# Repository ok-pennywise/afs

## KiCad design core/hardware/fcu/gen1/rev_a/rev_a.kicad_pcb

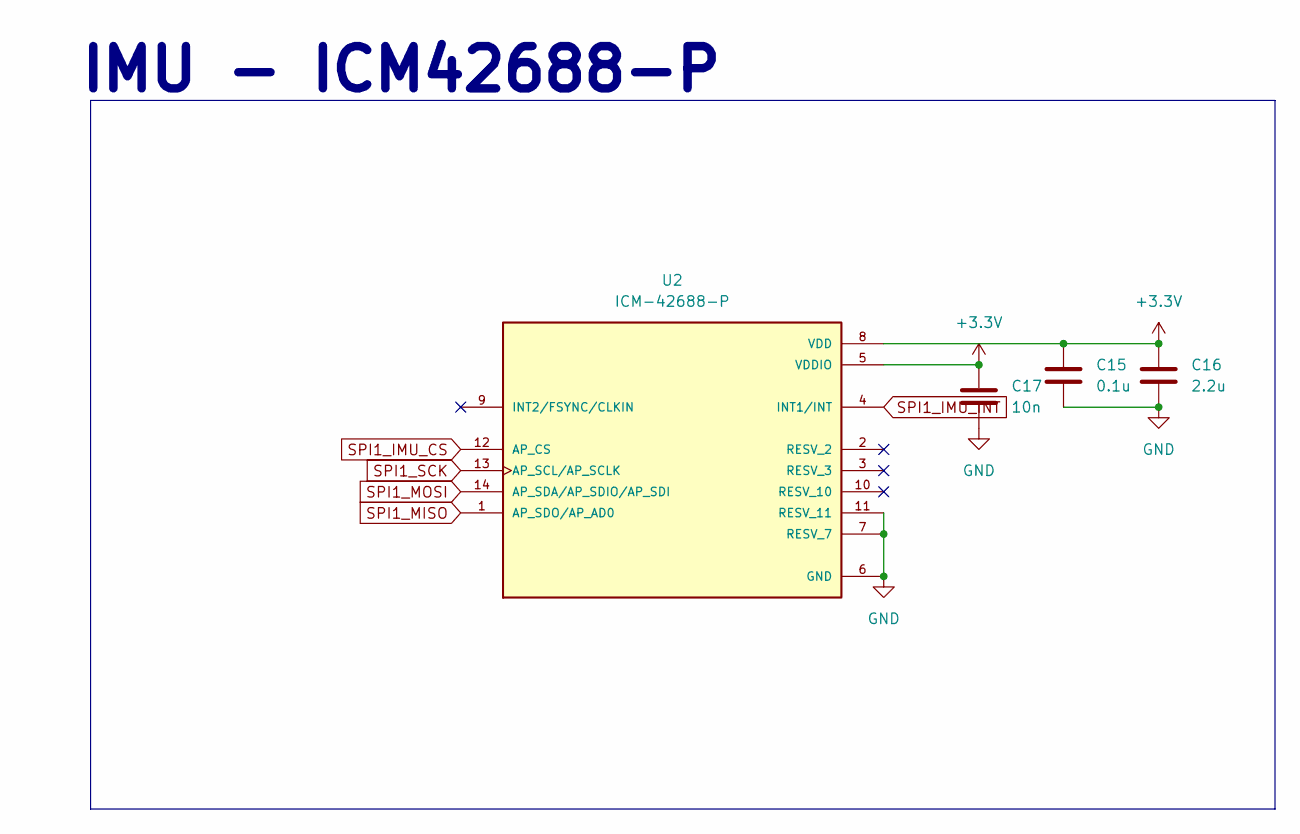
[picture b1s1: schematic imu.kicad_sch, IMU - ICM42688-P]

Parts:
C15: 0.1u; C_0603_1608Metric
C16: 2.2u; C_0603_1608Metric
C17: 10n; C_0603_1608Metric
U2: ICM-42688-P; PARTREV 1.2

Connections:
+3.3V: C15.1, C16.1, C17.1, U2.5 (VDDIO), U2.8 (VDD); also elsewhere on the board
GND: C15.2, C16.2, C17.2, U2.6 (GND), U2.7 (RESV_7), U2.11 (RESV_11); also elsewhere on the board
SPI1_IMU_CS: U2.12 (AP_CS); also elsewhere on the board
SPI1_IMU_INT: U2.4 (INT1/INT); also elsewhere on the board
SPI1_MISO: U2.1 (AP_SDO/AP_AD0); also elsewhere on the board
SPI1_MOSI: U2.14 (AP_SDA/AP_SDIO/AP_SDI); also elsewhere on the board
SPI1_SCK: U2.13 (AP_SCL/AP_SCLK); also elsewhere on the board

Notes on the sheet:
IMU - ICM42688-P

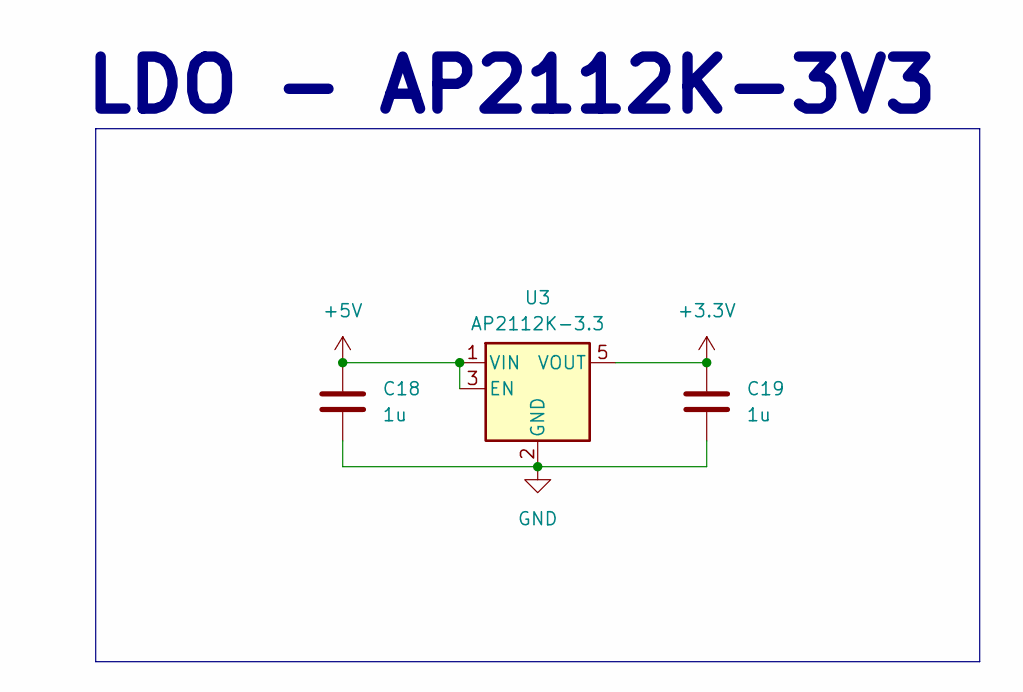
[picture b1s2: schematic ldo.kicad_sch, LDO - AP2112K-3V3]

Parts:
C18, C19: 1u; C_0603_1608Metric
U3: AP2112K-3.3; SOT-23-5

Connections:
+3.3V: C19.1, U3.5 (VOUT); also elsewhere on the board
+5V: C18.1, U3.1 (VIN), U3.3 (EN); also elsewhere on the board
GND: C18.2, C19.2, U3.2 (GND); also elsewhere on the board

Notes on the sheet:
LDO - AP2112K-3V3

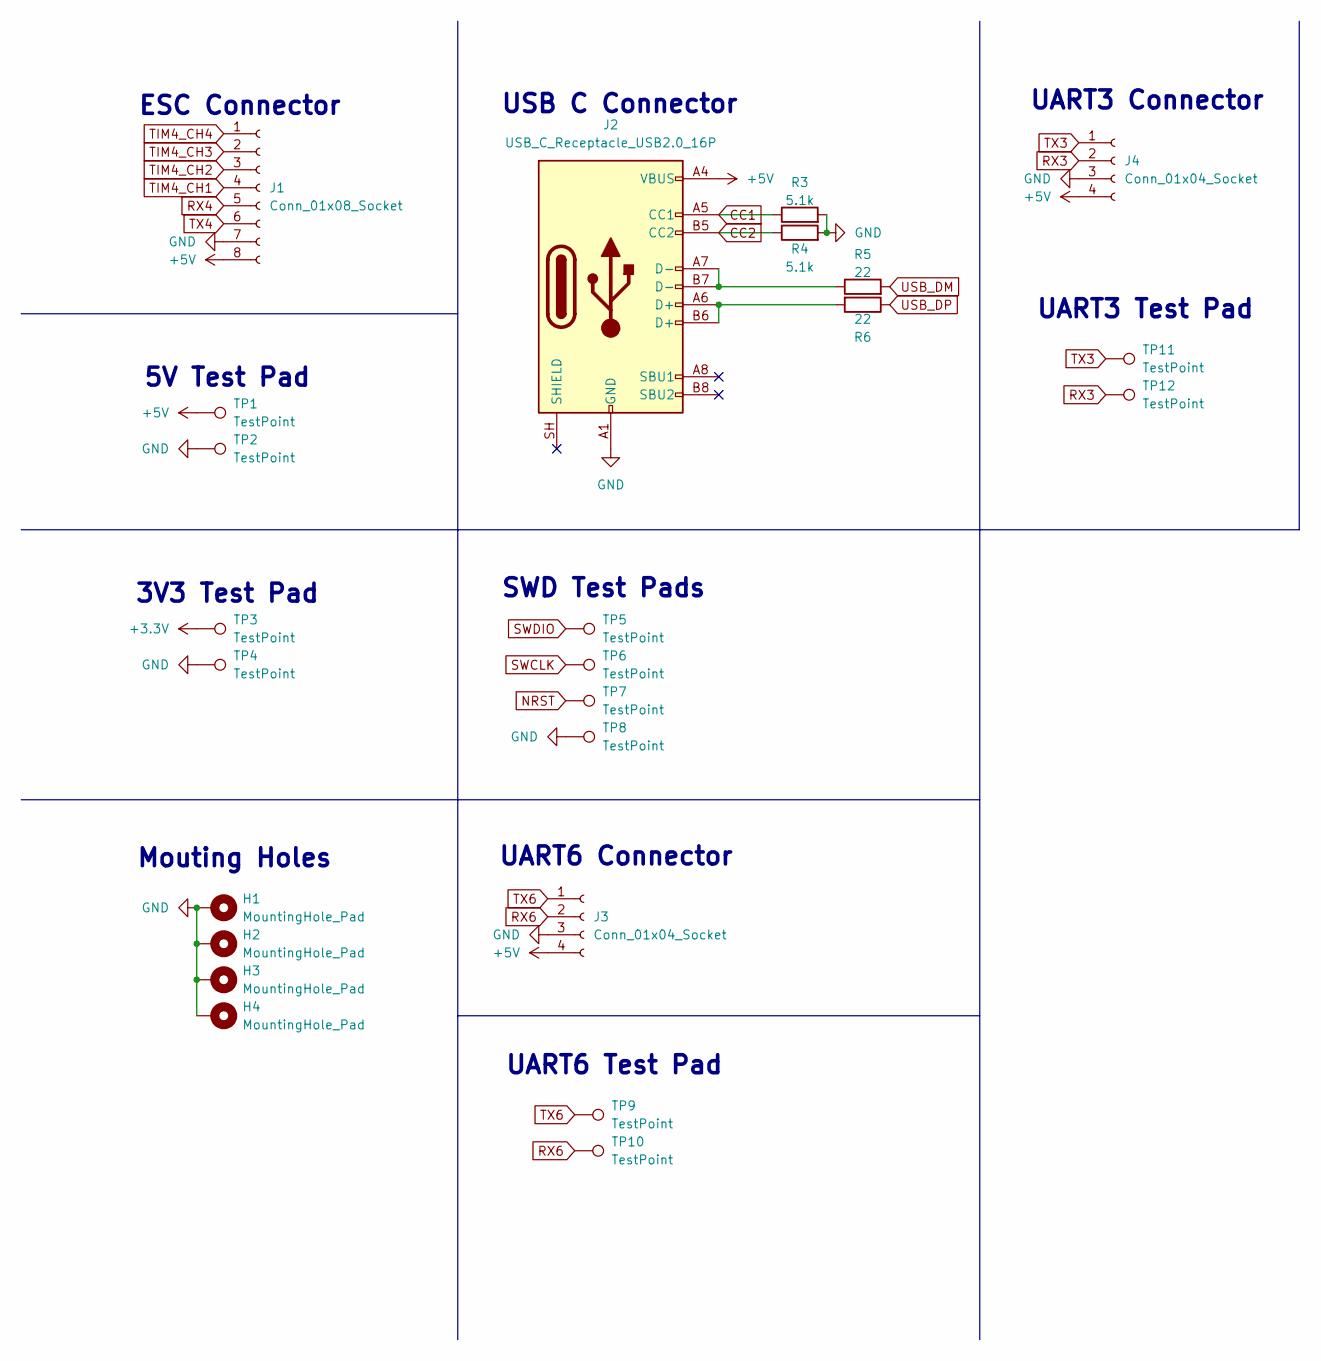
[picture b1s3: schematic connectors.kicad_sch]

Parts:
H1, H2, H3, H4: MountingHole_Pad; MountingHole_3.2mm_M3_Pad
J1: Conn_01x08_Socket; JST_SH_SM08B-SRSS-TB_1x08-1MP_P1.00mm_Horizontal
J2: USB_C_Receptacle_USB2.0_16P; USB_C_Receptacle_HRO_TYPE-C-31-M-12
J3, J4: Conn_01x04_Socket; JST_SH_SM04B-SRSS-TB_1x04-1MP_P1.00mm_Horizontal
R3, R4: 5.1k; R_0603_1608Metric
R5, R6: 22; R_0603_1608Metric
TP1, TP2, TP3, TP4: TestPoint; TestPoint_Pad_2.5x2.5mm
TP5, TP6, TP7, TP8, TP9, TP10, TP11, TP12: TestPoint; TestPoint_Pad_1.5x1.5mm

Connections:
+3.3V: TP3.1 (1_1); also elsewhere on the board
+5V: J1.8, J2.A4 (VBUS), J2.A9 (VBUS), J2.B4 (VBUS), J2.B9 (VBUS), J3.4, J4.4, TP1.1 (1_1); also elsewhere on the board
CC1: J2.A5 (CC1), R3.1
CC2: J2.B5 (CC2), R4.1
GND: H1.1 (1_1), H2.1 (1_1), H3.1 (1_1), H4.1 (1_1), J1.7, J2.A1 (GND), J2.A12 (GND), J2.B1 (GND), J2.B12 (GND), J3.3, J4.3, R3.2, R4.2, TP2.1 (1_1), TP4.1 (1_1), TP8.1 (1_1); also elsewhere on the board
NRST: TP7.1 (1_1); also elsewhere on the board
unnamed: J2.A6 (D+), J2.B6 (D+), R6.2
unnamed: J2.A7 (D-), J2.B7 (D-), R5.1
RX3: J4.2, TP12.1 (1_1); also elsewhere on the board
RX4: J1.5; also elsewhere on the board
RX6: J3.2, TP10.1 (1_1); also elsewhere on the board
SWCLK: TP6.1 (1_1); also elsewhere on the board
SWDIO: TP5.1 (1_1); also elsewhere on the board
TIM4_CH1: J1.4; also elsewhere on the board
TIM4_CH2: J1.3; also elsewhere on the board
TIM4_CH3: J1.2; also elsewhere on the board
TIM4_CH4: J1.1; also elsewhere on the board
TX3: J4.1, TP11.1 (1_1); also elsewhere on the board
TX4: J1.6; also elsewhere on the board
TX6: J3.1, TP9.1 (1_1); also elsewhere on the board
USB_DM: R5.2; also elsewhere on the board
USB_DP: R6.1; also elsewhere on the board

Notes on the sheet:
ESC Connector
USB C Connector
SWD Test Pads
UART6 Test Pad
Mouting Holes
UART3 Connector
5V Test Pad
UART3 Test Pad
UART6 Connector
3V3 Test Pad

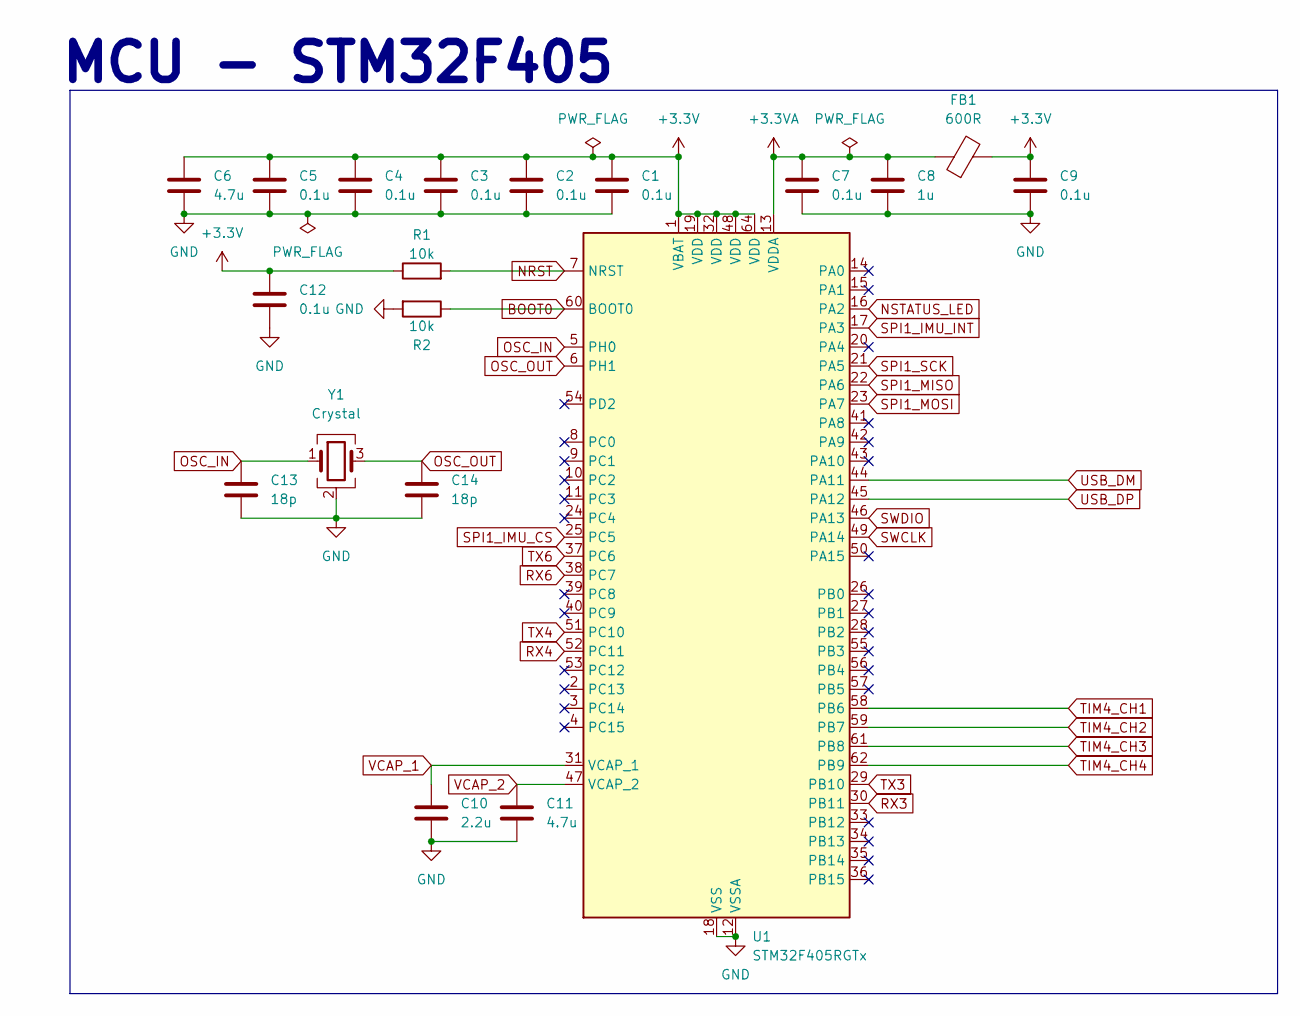
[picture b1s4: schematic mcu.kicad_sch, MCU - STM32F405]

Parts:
C1, C2, C3, C4, C5, C7, C9, C12: 0.1u; C_0603_1608Metric
C6, C11: 4.7u; C_0603_1608Metric
C8: 1u; C_0603_1608Metric
C10: 2.2u; C_0603_1608Metric
C13, C14: 18p; C_0805_2012Metric
FB1: 600R; L_0603_1608Metric
R1, R2: 10k; R_0603_1608Metric
U1: STM32F405RGTx; LQFP-64_10x10mm_P0.5mm
Y1: Crystal; Crystal_SMD_5032-4Pin_5.0x3.2mm

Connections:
+3.3V: C1.1, C2.1, C3.1, C4.1, C5.1, C6.1, C9.1, C12.1, FB1.2, R1.1, U1.1 (VBAT), U1.19 (VDD), U1.32 (VDD), U1.48 (VDD), U1.64 (VDD); also elsewhere on the board
+3.3VA: C7.1, C8.1, FB1.1, U1.13 (VDDA)
BOOT0: R2.1, U1.60 (BOOT0)
GND: C1.2, C2.2, C3.2, C4.2, C5.2, C6.2, C7.2, C8.2, C9.2, C10.2, C11.2, C12.2, C13.2, C14.2, R2.2, U1.12 (VSSA), U1.18 (VSS), U1.63 (VSS), Y1.2 (G), Y1.4 (G); also elsewhere on the board
NRST: R1.2, U1.7 (NRST); also elsewhere on the board
NSTATUS_LED: U1.16 (PA2); also elsewhere on the board
OSC_IN: C13.1, U1.5 (PH0), Y1.1
OSC_OUT: C14.1, U1.6 (PH1), Y1.3
RX3: U1.30 (PB11); also elsewhere on the board
RX4: U1.52 (PC11); also elsewhere on the board
RX6: U1.38 (PC7); also elsewhere on the board
SPI1_IMU_CS: U1.25 (PC5); also elsewhere on the board
SPI1_IMU_INT: U1.17 (PA3); also elsewhere on the board
SPI1_MISO: U1.22 (PA6); also elsewhere on the board
SPI1_MOSI: U1.23 (PA7); also elsewhere on the board
SPI1_SCK: U1.21 (PA5); also elsewhere on the board
SWCLK: U1.49 (PA14); also elsewhere on the board
SWDIO: U1.46 (PA13); also elsewhere on the board
TIM4_CH1: U1.58 (PB6); also elsewhere on the board
TIM4_CH2: U1.59 (PB7); also elsewhere on the board
TIM4_CH3: U1.61 (PB8); also elsewhere on the board
TIM4_CH4: U1.62 (PB9); also elsewhere on the board
TX3: U1.29 (PB10); also elsewhere on the board
TX4: U1.51 (PC10); also elsewhere on the board
TX6: U1.37 (PC6); also elsewhere on the board
USB_DM: U1.44 (PA11); also elsewhere on the board
USB_DP: U1.45 (PA12); also elsewhere on the board
VCAP_1: C10.1, U1.31 (VCAP_1)
VCAP_2: C11.1, U1.47 (VCAP_2)

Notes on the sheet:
MCU - STM32F405

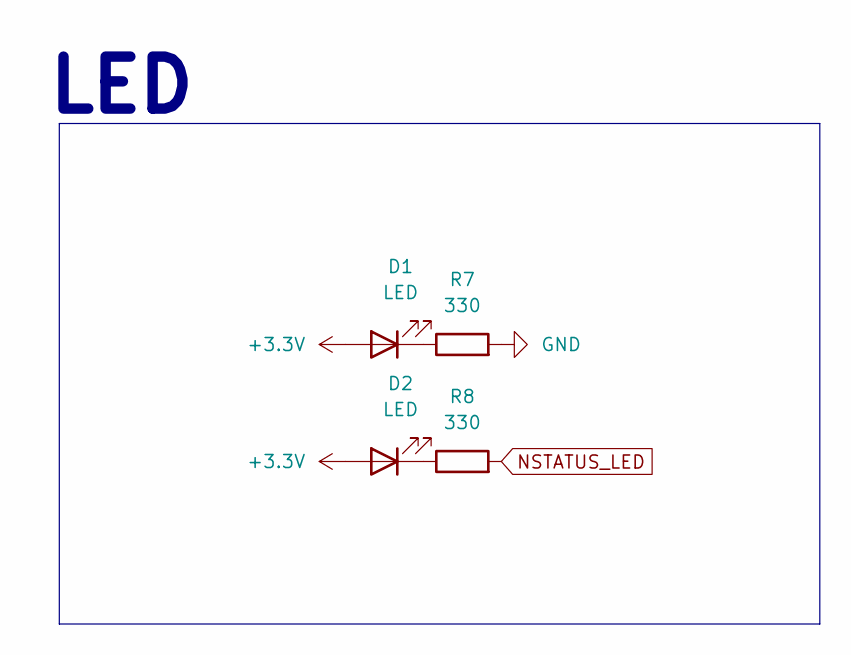
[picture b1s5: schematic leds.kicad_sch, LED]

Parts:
D1, D2: LED; LED_0603_1608Metric
R7, R8: 330; R_0603_1608Metric

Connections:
+3.3V: D1.2 (A), D2.2 (A); also elsewhere on the board
GND: R7.2; also elsewhere on the board
NSTATUS_LED: R8.2; also elsewhere on the board
unnamed: D1.1 (K), R7.1
unnamed: D2.1 (K), R8.1

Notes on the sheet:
LED

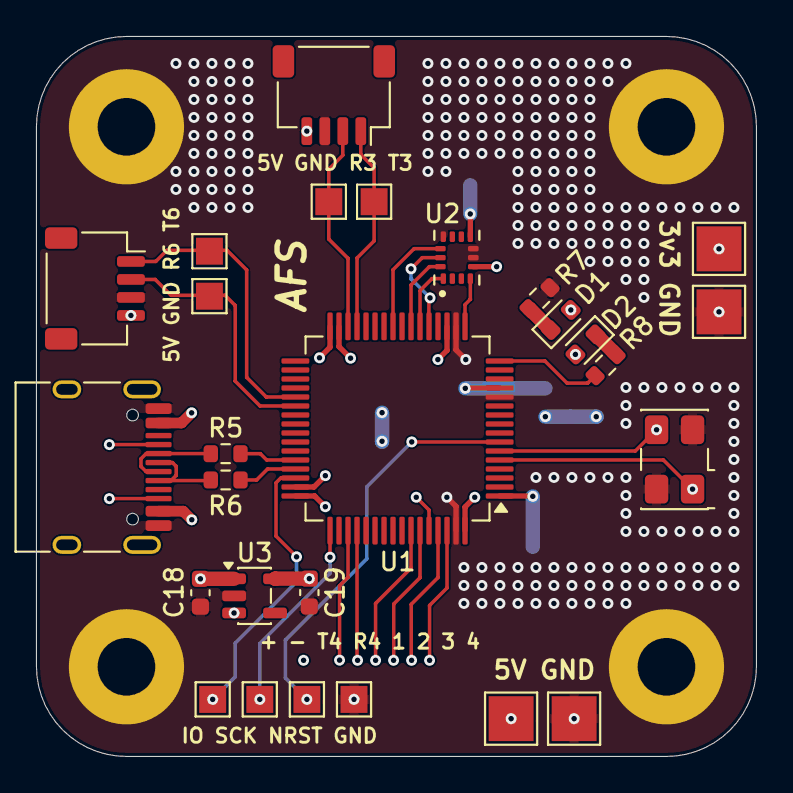
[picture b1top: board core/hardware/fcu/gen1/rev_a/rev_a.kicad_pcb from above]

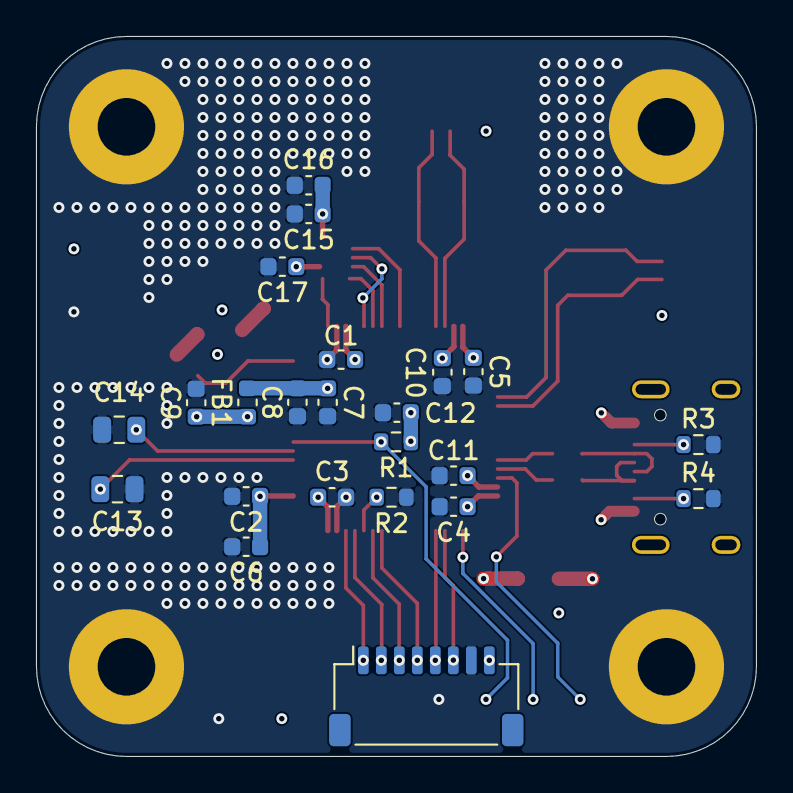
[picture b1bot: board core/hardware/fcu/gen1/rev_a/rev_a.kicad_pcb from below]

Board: 4 copper layers, 40.0 x 40.0 mm, 54 parts (23 on the bottom side), 36 nets.

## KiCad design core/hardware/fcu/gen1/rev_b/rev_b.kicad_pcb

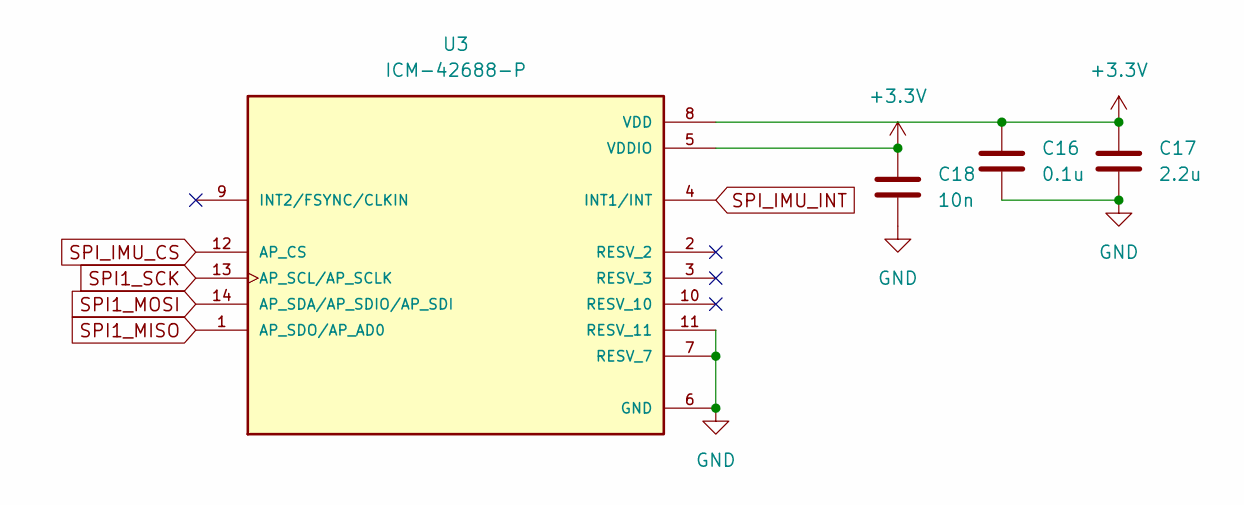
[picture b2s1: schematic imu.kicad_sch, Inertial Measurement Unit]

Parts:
C16: 0.1u; C_0603_1608Metric
C17: 2.2u; C_0603_1608Metric
C18: 10n; C_0603_1608Metric
U3: ICM-42688-P; PQFN50P300X250X97-14N; PARTREV 1.2

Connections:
+3.3V: C16.1, C17.1, C18.1, U3.5 (VDDIO), U3.8 (VDD); also elsewhere on the board
GND: C16.2, C17.2, C18.2, U3.6 (GND), U3.7 (RESV_7), U3.11 (RESV_11); also elsewhere on the board
SPI1_MISO: U3.1 (AP_SDO/AP_AD0); also elsewhere on the board
SPI1_MOSI: U3.14 (AP_SDA/AP_SDIO/AP_SDI); also elsewhere on the board
SPI1_SCK: U3.13 (AP_SCL/AP_SCLK); also elsewhere on the board
SPI_IMU_CS: U3.12 (AP_CS); also elsewhere on the board
SPI_IMU_INT: U3.4 (INT1/INT); also elsewhere on the board

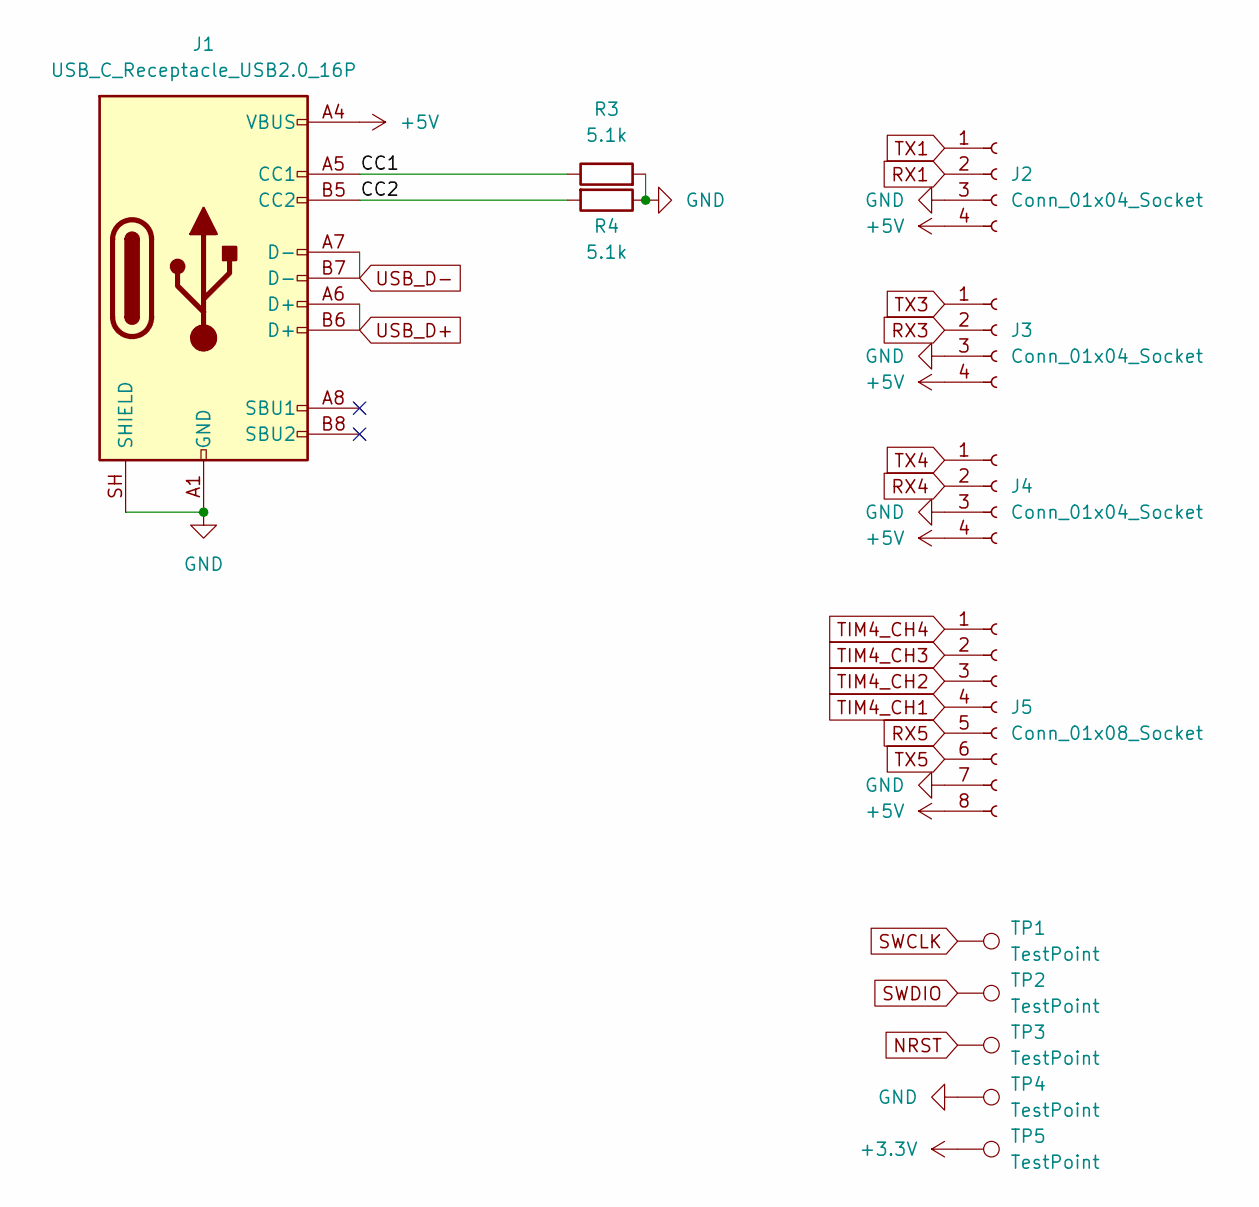
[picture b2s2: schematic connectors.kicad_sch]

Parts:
J1: USB_C_Receptacle_USB2.0_16P; USB_C_Receptacle_GCT_USB4105-xx-A_16P_TopMnt_Horizontal
J2, J3, J4: Conn_01x04_Socket; JST_SH_SM04B-SRSS-TB_1x04-1MP_P1.00mm_Horizontal
J5: Conn_01x08_Socket; JST_SH_SM08B-SRSS-TB_1x08-1MP_P1.00mm_Horizontal
R3, R4: 5.1k; R_0603_1608Metric
TP1, TP2, TP3, TP4, TP5: TestPoint; TestPoint_THTPad_1.5x1.5mm_Drill0.7mm

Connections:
+3.3V: TP5.1 (1_1); also elsewhere on the board
+5V: J1.A4 (VBUS), J1.A9 (VBUS), J1.B4 (VBUS), J1.B9 (VBUS), J2.4, J3.4, J4.4, J5.8; also elsewhere on the board
/Connectors/CC1: J1.A5 (CC1), R3.1
/Connectors/CC2: J1.B5 (CC2), R4.2
GND: J1.A1 (GND), J1.A12 (GND), J1.B1 (GND), J1.B12 (GND), J1.SH (SHIELD), J2.3, J3.3, J4.3, J5.7, R3.2, R4.1, TP4.1 (1_1); also elsewhere on the board
NRST: TP3.1 (1_1); also elsewhere on the board
RX1: J2.2; also elsewhere on the board
RX3: J3.2; also elsewhere on the board
RX4: J4.2; also elsewhere on the board
RX5: J5.5; also elsewhere on the board
SWCLK: TP1.1 (1_1); also elsewhere on the board
SWDIO: TP2.1 (1_1); also elsewhere on the board
TIM4_CH1: J5.4; also elsewhere on the board
TIM4_CH2: J5.3; also elsewhere on the board
TIM4_CH3: J5.2; also elsewhere on the board
TIM4_CH4: J5.1; also elsewhere on the board
TX1: J2.1; also elsewhere on the board
TX3: J3.1; also elsewhere on the board
TX4: J4.1; also elsewhere on the board
TX5: J5.6; also elsewhere on the board
USB_D+: J1.A6 (D+), J1.B6 (D+); also elsewhere on the board
USB_D-: J1.A7 (D-), J1.B7 (D-); also elsewhere on the board

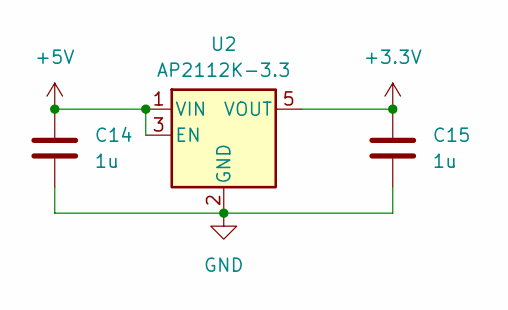
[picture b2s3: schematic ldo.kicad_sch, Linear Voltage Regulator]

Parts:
C14, C15: 1u; C_0603_1608Metric
U2: AP2112K-3.3; SOT-23-5

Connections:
+3.3V: C15.1, U2.5 (VOUT); also elsewhere on the board
+5V: C14.1, U2.1 (VIN), U2.3 (EN); also elsewhere on the board
GND: C14.2, C15.2, U2.2 (GND); also elsewhere on the board

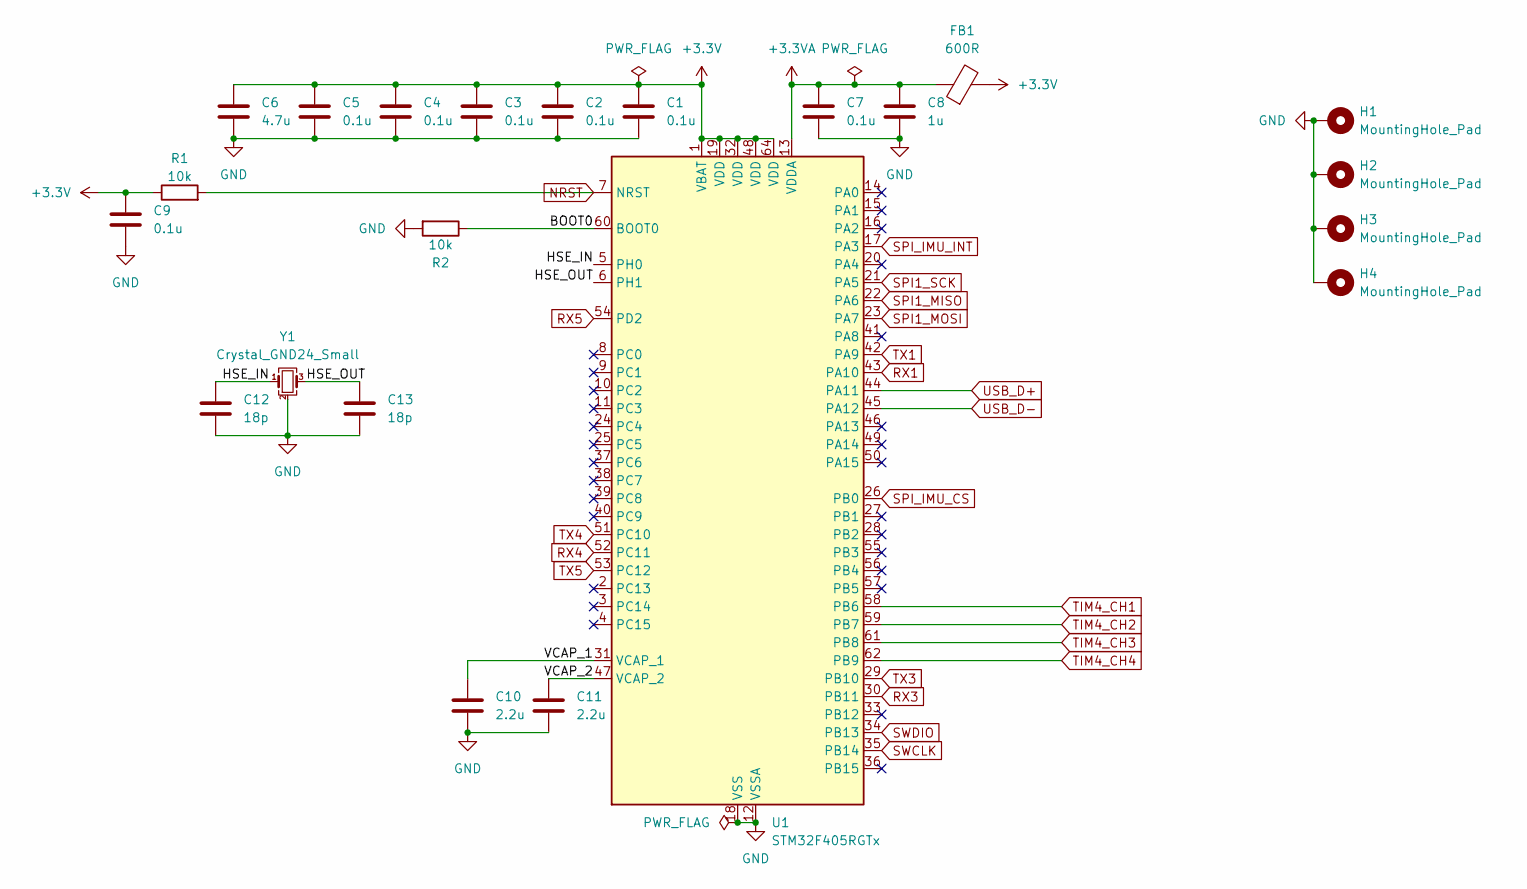
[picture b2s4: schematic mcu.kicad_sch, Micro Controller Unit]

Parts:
C1, C2, C3, C4, C5, C7, C9: 0.1u; C_0603_1608Metric
C6: 4.7u; C_0603_1608Metric
C8: 1u; C_0603_1608Metric
C10, C11: 2.2u; C_0603_1608Metric
C12, C13: 18p; C_0805_2012Metric
FB1: 600R; L_0603_1608Metric
H1, H2, H3, H4: MountingHole_Pad; MountingHole_3.2mm_M3_Pad
R1, R2: 10k; R_0603_1608Metric
U1: STM32F405RGTx; LQFP-64_10x10mm_P0.5mm
Y1: Crystal_GND24_Small; Crystal_SMD_3225-4Pin_3.2x2.5mm

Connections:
+3.3V: C1.1, C2.1, C3.1, C4.1, C5.1, C6.1, C9.1, FB1.2, R1.1, U1.1 (VBAT), U1.19 (VDD), U1.32 (VDD), U1.48 (VDD), U1.64 (VDD); also elsewhere on the board
+3.3VA: C7.1, C8.1, FB1.1, U1.13 (VDDA)
/MCU/BOOT0: R2.1, U1.60 (BOOT0)
/MCU/HSE_IN: C12.1, U1.5 (PH0), Y1.1
/MCU/HSE_OUT: C13.1, U1.6 (PH1), Y1.3
/MCU/VCAP_1: C10.1, U1.31 (VCAP_1)
/MCU/VCAP_2: C11.1, U1.47 (VCAP_2)
GND: C1.2, C2.2, C3.2, C4.2, C5.2, C6.2, C7.2, C8.2, C9.2, C10.2, C11.2, C12.2, C13.2, H1.1 (1_1), H2.1 (1_1), H3.1 (1_1), H4.1 (1_1), R2.2, U1.12 (VSSA), U1.18 (VSS), U1.63 (VSS), Y1.2 (G), Y1.4 (G); also elsewhere on the board
NRST: R1.2, U1.7 (NRST); also elsewhere on the board
RX1: U1.43 (PA10); also elsewhere on the board
RX3: U1.30 (PB11); also elsewhere on the board
RX4: U1.52 (PC11); also elsewhere on the board
RX5: U1.54 (PD2); also elsewhere on the board
SPI1_MISO: U1.22 (PA6); also elsewhere on the board
SPI1_MOSI: U1.23 (PA7); also elsewhere on the board
SPI1_SCK: U1.21 (PA5); also elsewhere on the board
SPI_IMU_CS: U1.26 (PB0); also elsewhere on the board
SPI_IMU_INT: U1.17 (PA3); also elsewhere on the board
SWCLK: U1.35 (PB14); also elsewhere on the board
SWDIO: U1.34 (PB13); also elsewhere on the board
TIM4_CH1: U1.58 (PB6); also elsewhere on the board
TIM4_CH2: U1.59 (PB7); also elsewhere on the board
TIM4_CH3: U1.61 (PB8); also elsewhere on the board
TIM4_CH4: U1.62 (PB9); also elsewhere on the board
TX1: U1.42 (PA9); also elsewhere on the board
TX3: U1.29 (PB10); also elsewhere on the board
TX4: U1.51 (PC10); also elsewhere on the board
TX5: U1.53 (PC12); also elsewhere on the board
USB_D+: U1.44 (PA11); also elsewhere on the board
USB_D-: U1.45 (PA12); also elsewhere on the board

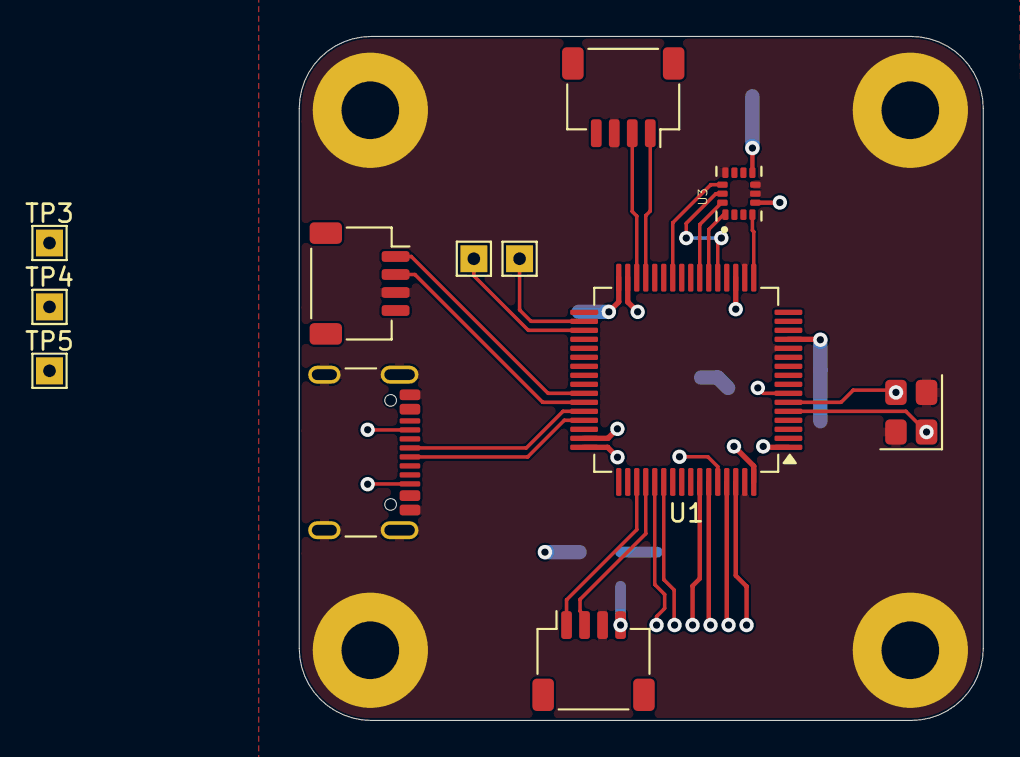
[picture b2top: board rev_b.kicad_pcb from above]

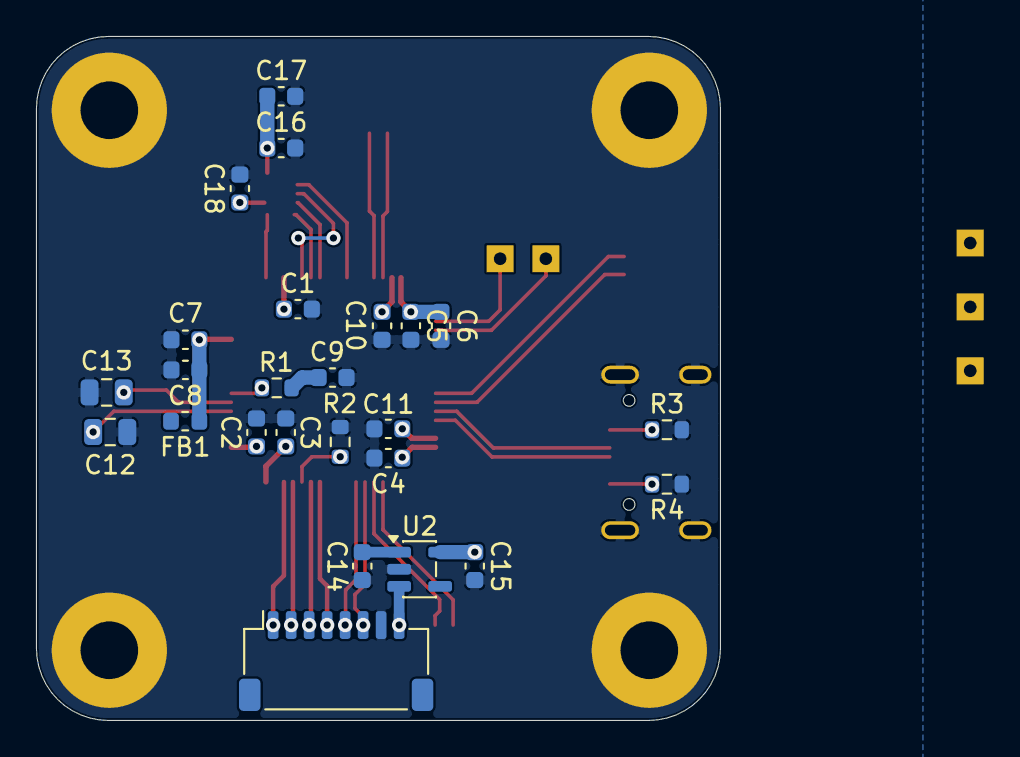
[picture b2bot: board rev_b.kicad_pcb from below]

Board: 4 copper layers, 38.0 x 38.0 mm, 41 parts (25 on the bottom side), 33 nets.

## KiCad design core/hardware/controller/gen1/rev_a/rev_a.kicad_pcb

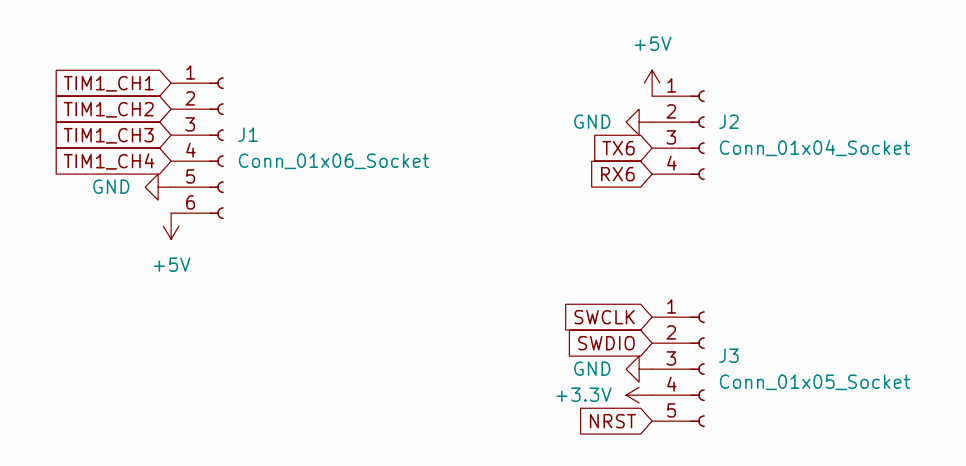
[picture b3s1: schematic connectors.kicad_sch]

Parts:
J1: Conn_01x06_Socket; PinHeader_1x06_P2.54mm_Horizontal
J2: Conn_01x04_Socket; PinHeader_1x04_P2.54mm_Horizontal
J3: Conn_01x05_Socket; PinHeader_1x05_P2.54mm_Horizontal

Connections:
+3.3V: J3.4; also elsewhere on the board
+5V: J1.6, J2.1; also elsewhere on the board
GND: J1.5, J2.2, J3.3; also elsewhere on the board
NRST: J3.5; also elsewhere on the board
RX6: J2.4; also elsewhere on the board
SWCLK: J3.1; also elsewhere on the board
SWDIO: J3.2; also elsewhere on the board
TIM1_CH1: J1.1; also elsewhere on the board
TIM1_CH2: J1.2; also elsewhere on the board
TIM1_CH3: J1.3; also elsewhere on the board
TIM1_CH4: J1.4; also elsewhere on the board
TX6: J2.3; also elsewhere on the board

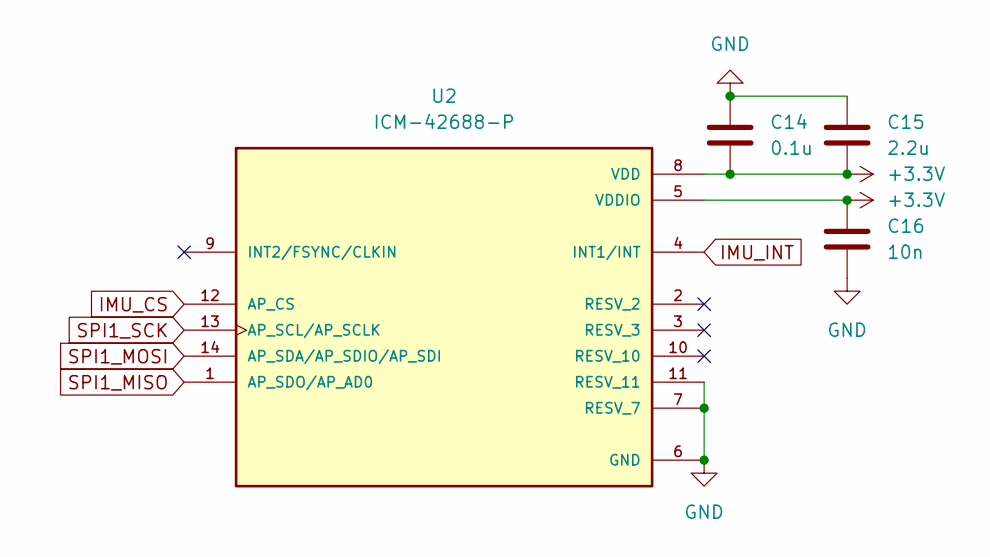
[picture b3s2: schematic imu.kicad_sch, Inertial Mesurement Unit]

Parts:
C14: 0.1u; C_0603_1608Metric_Pad1.08x0.95mm_HandSolder
C15: 2.2u; C_0603_1608Metric_Pad1.08x0.95mm_HandSolder
C16: 10n; C_0603_1608Metric_Pad1.08x0.95mm_HandSolder
U2: ICM-42688-P; PARTREV 1.2

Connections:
+3.3V: C14.2, C15.2, C16.1, U2.5 (VDDIO), U2.8 (VDD); also elsewhere on the board
GND: C14.1, C15.1, C16.2, U2.6 (GND), U2.7 (RESV_7), U2.11 (RESV_11); also elsewhere on the board
IMU_CS: U2.12 (AP_CS); also elsewhere on the board
IMU_INT: U2.4 (INT1/INT); also elsewhere on the board
SPI1_MISO: U2.1 (AP_SDO/AP_AD0); also elsewhere on the board
SPI1_MOSI: U2.14 (AP_SDA/AP_SDIO/AP_SDI); also elsewhere on the board
SPI1_SCK: U2.13 (AP_SCL/AP_SCLK); also elsewhere on the board

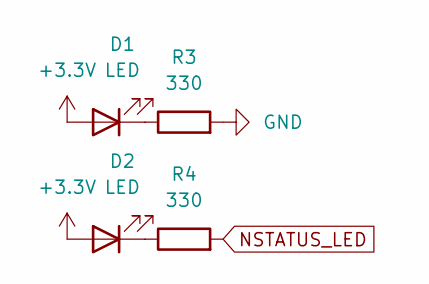
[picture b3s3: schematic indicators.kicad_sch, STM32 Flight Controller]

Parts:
D1, D2: LED; LED_0603_1608Metric_Pad1.05x0.95mm_HandSolder
R3, R4: 330; R_0603_1608Metric_Pad0.98x0.95mm_HandSolder

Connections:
+3.3V: D1.2 (A), D2.2 (A); also elsewhere on the board
GND: R3.2; also elsewhere on the board
NSTATUS_LED: R4.2; also elsewhere on the board
unnamed: D1.1 (K), R3.1
unnamed: D2.1 (K), R4.1

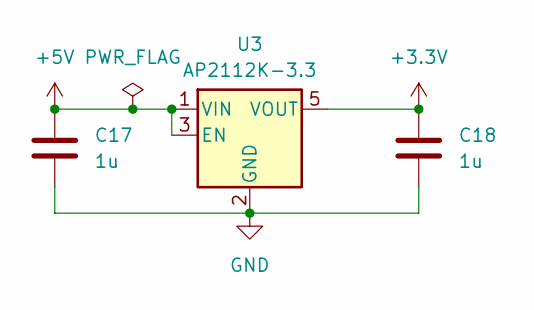
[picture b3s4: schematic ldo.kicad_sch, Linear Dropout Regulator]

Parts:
C17, C18: 1u; C_0603_1608Metric_Pad1.08x0.95mm_HandSolder
U3: AP2112K-3.3; SOT-23-5

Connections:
+3.3V: C18.1, U3.5 (VOUT); also elsewhere on the board
+5V: C17.1, U3.1 (VIN), U3.3 (EN); also elsewhere on the board
GND: C17.2, C18.2, U3.2 (GND); also elsewhere on the board
